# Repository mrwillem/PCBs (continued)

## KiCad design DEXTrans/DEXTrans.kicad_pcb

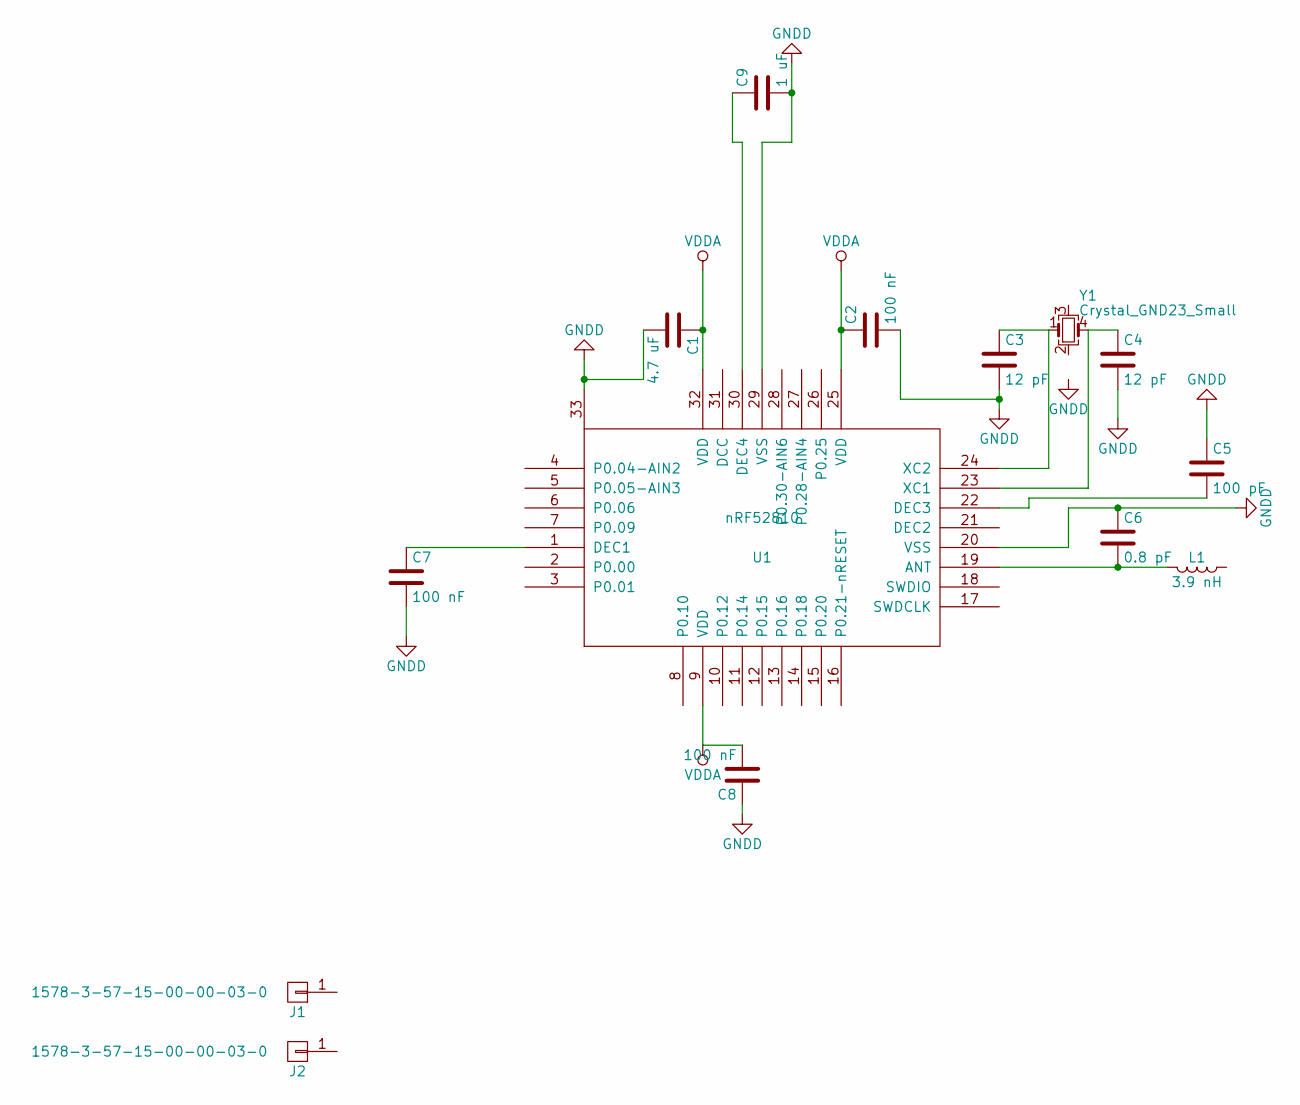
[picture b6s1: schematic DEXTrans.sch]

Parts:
C1: 4.7 uF; C_0603
C2, C7, C8: 100 nF; R_0402_HandSoldering
C3, C4: 12 pF; R_0402_HandSoldering
C5: 100 pF; R_0402_HandSoldering
C6: 0.8 pF; R_0402_HandSoldering
C9: 1 uF; C_0603
J1, J2: 1578-3-57-15-00-00-03-0; MillMax1578_Disc_Connector
L1: 3.9 nH; R_0402_HandSoldering
U1: nRF52810; QFN-32-1EP_5x5mm_Pitch0.5mm_HandSolder
Y1: Crystal_GND23_Small; Oscillator_SMD_SeikoEpson_SG210-4pin_2.5x2.0mm

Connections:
GNDD: C1.2, C2.2, C3.2, C4.2, C5.1, C6.1, C7.2, C8.1, C9.2, U1.20 (VSS), U1.29 (VSS), U1.33
unnamed: C3.1, U1.24 (XC2), Y1.1
unnamed: C4.1, U1.23 (XC1), Y1.4
unnamed: C5.2, U1.22 (DEC3)
unnamed: C6.2, L1.2, U1.19 (ANT)
unnamed: C7.1, U1.1 (DEC1)
unnamed: C9.1, U1.30 (DEC4)
VDDA: C1.1, C2.1, C8.2, U1.9 (VDD), U1.25 (VDD), U1.32 (VDD)

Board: 2 copper layers, 14 parts (0 on the bottom side), 8 nets, no tracks yet.

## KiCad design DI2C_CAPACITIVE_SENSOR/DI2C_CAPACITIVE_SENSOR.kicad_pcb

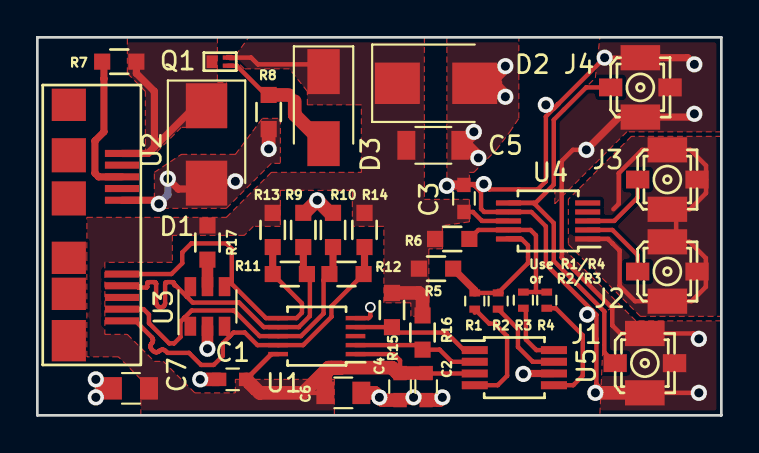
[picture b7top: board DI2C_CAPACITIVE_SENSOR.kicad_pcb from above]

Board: 2 copper layers, 38.0 x 21.0 mm, 37 parts (0 on the bottom side), 22 nets.

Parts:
C1, C2, C3, C4: C; C_0603
C5: 10uF; C_1206
C6: 4,7uF; C_0805
C7: 2,2uF; C_0805
D1: ATV06B5V0JB-HF; D_SMB
D2: 1SMB5913BT3G; D_SMB
D3: D; D_SMA
J1, J2, J3, J4: CONN_01X02; Amphenol_A1-JB_U.FL
Q1: DMP58D0LFB; X1-DFN1006-3
R1, R2, R3, R4: R; R_0402
R5, R6, R15, R16: 2K2; R_0603_HandSolder
R7, R8, R9, R10, R11, R12, R13, R14: R; R_0603_HandSolder
R17: 0R0; R_0603_HandSolder
U1: PCA9615; TSSOP-10_3x3mm_Pitch0.5mm
U2: Micro_USB3_GSB343133HR; USB_Micro-3_GSB343133HR
U3: WE824013; SOT-23-6
U4: FDC1004; MSOP-10_3x3mm_Pitch0.5mm
U5: PI4MSD5V9540; MSOP-8_3x3mm_Pitch0.65mm

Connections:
+3V3: C1.2, C2.2, C3.1, C4.1, C5.1, C6.1, C7.1, D2.1, D3.1, Q1.2, R5.2, R6.1, R13.2, R14.2, R15.2, R16.2, R17.1, U1.1, U1.10, U4.8, U5.3
CIN1: J2.1, U4.2
CIN2: J3.1, U4.3
GND: C1.1, C2.1, C3.2, C4.2, C5.2, C6.2, C7.2, D1.2, D2.2, J1.2, J4.2, R8.1, R9.1, R10.1, U1.5, U2.5, U2.8, U3.2, U4.7, U5.6
unnamed: D3.2, Q1.1, R8.2
unnamed: R1.2, R3.2, R5.1, U4.10
unnamed: R2.2, R4.2, R6.2, U4.9
unnamed: R7.2, U2.3
unnamed: R17.2, U3.5
SC0: R4.1, U5.5
SC1: R2.1, U5.8
SCL: R15.1, U1.4, U5.1
SCL+: R11.2, R13.1, U1.6, U2.6, U3.4
SCL-: R9.2, R11.1, U1.7, U2.7, U3.6
SD0: R3.1, U5.4
SD1: R1.1, U5.7
SDA: R16.1, U1.2, U5.2
SDA+: R12.2, R14.1, U1.9, U2.10, U3.3
SDA-: R10.2, R12.1, U1.8, U2.9, U3.1
SHLD1: J2.2, J3.2, U4.1
SHLD2: J1.1, J4.1, U4.6
VSRC: D1.1, Q1.3, R7.1, U2.1
